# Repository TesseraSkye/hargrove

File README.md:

# Hargrove: a hybrid digital / analog synth

Built with Supercollider and Electron. 
GPL3 licence.

~~ IN DEVELOPMENT ~~

Install Supercollider and the SC3 plugins to the default directory.
https://supercollider.github.io/
https://supercollider.github.io/sc3-plugins/

 Windows firewall makes a mess of things, so add an exception:
 https://support.microsoft.com/help/4028485

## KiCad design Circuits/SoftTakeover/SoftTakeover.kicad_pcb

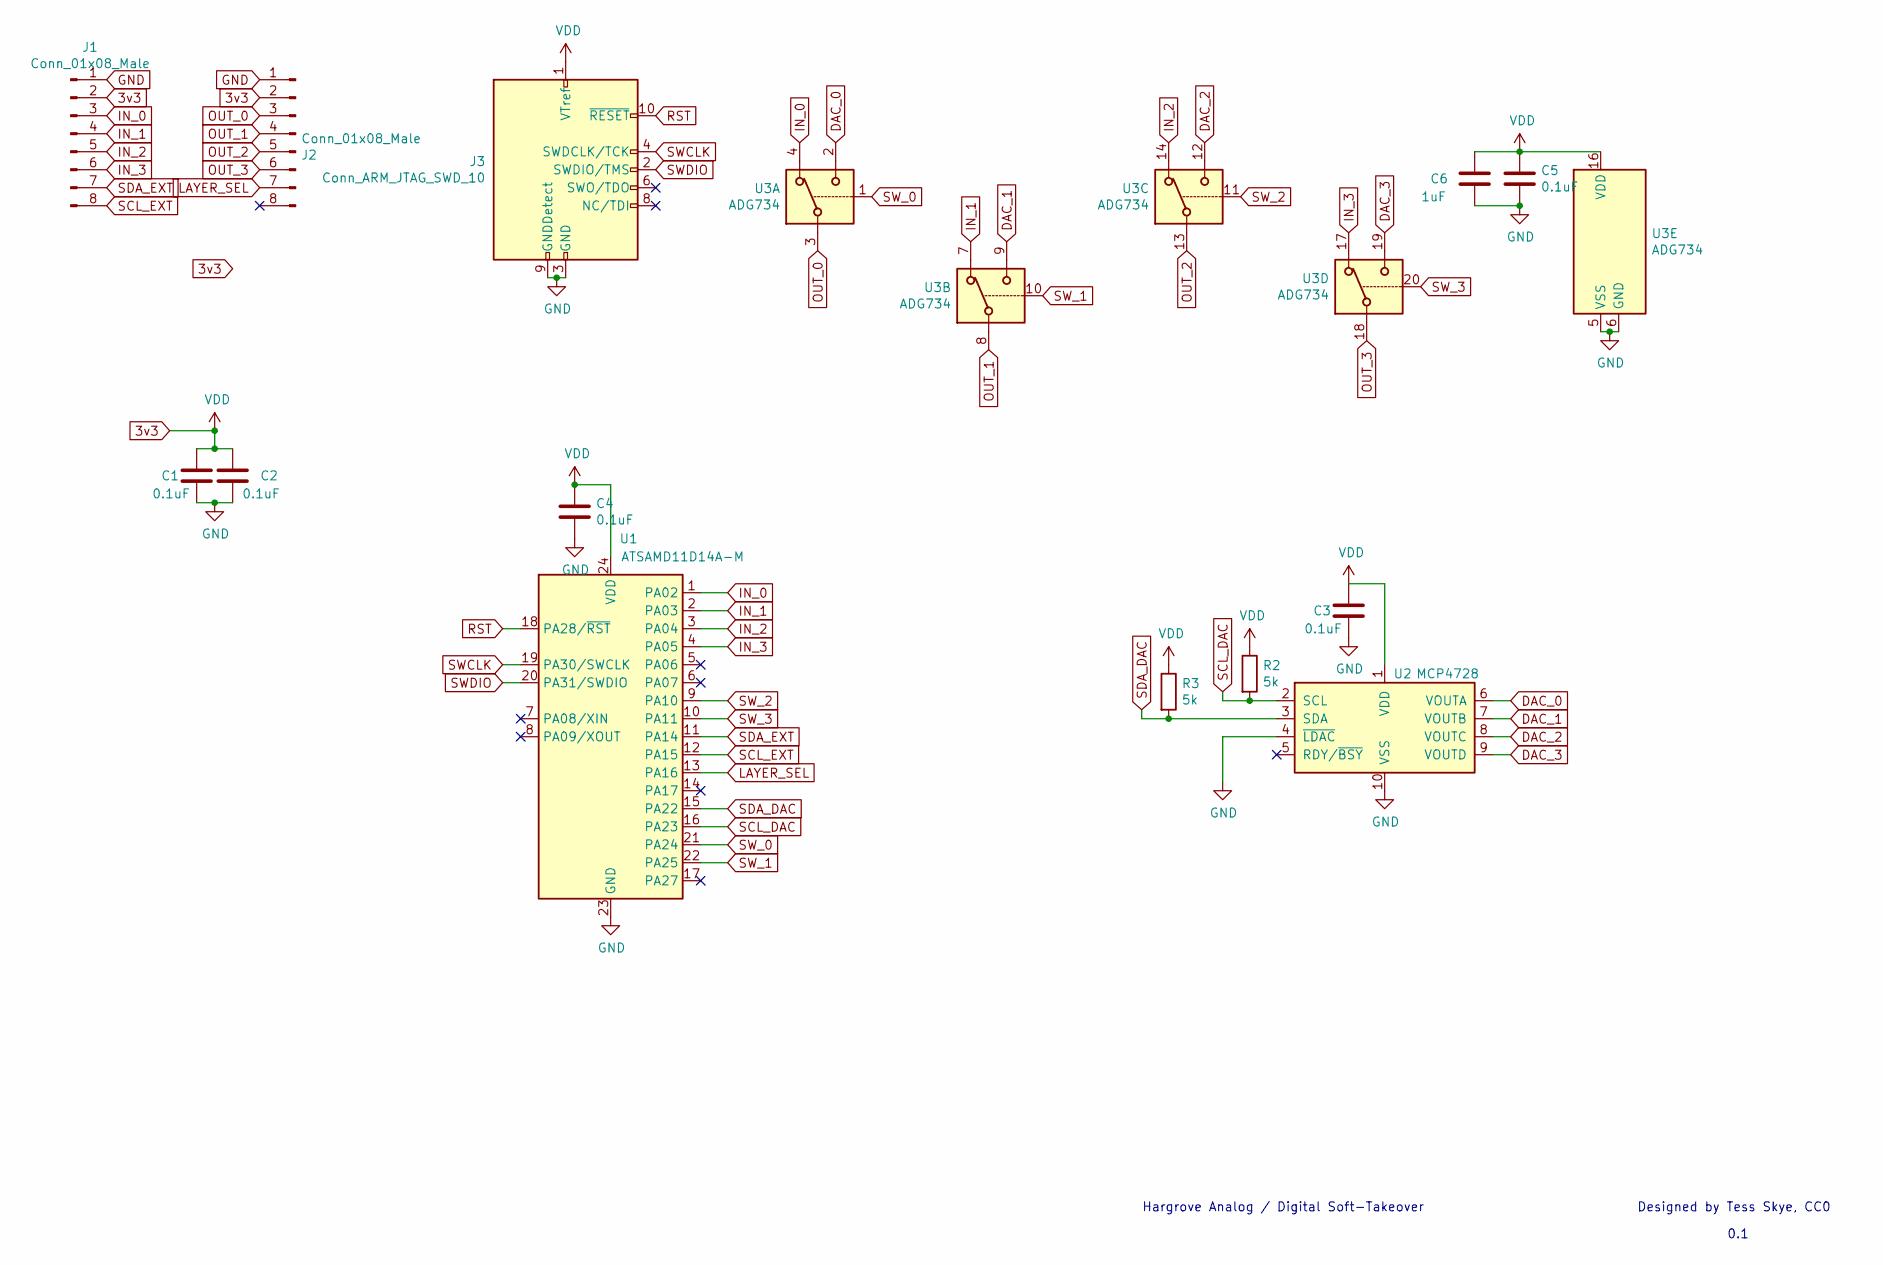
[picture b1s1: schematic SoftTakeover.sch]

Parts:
C1, C2, C3, C4, C5: 0.1uF; C_0603_1608Metric
C6: 1uF; C_0603_1608Metric
J1, J2: Conn_01x08_Male; PinHeader_1x08_P2.54mm_Vertical
J3: Conn_ARM_JTAG_SWD_10; PinHeader_2x05_P1.27mm_Vertical
R2, R3: 5k; R_0603_1608Metric
U1: ATSAMD11D14A-M; QFN-24-1EP_4x4mm_P0.5mm_EP2.6x2.6mm
U2: MCP4728; MSOP-10_3x3mm_P0.5mm
U3: ADG734; TSSOP-20_4.4x6.5mm_P0.65mm

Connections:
3v3: C1.2, C2.2, C3.2, C4.2, C5.1, C6.1, J1.2, J2.2, J3.1 (VTref), R2.1, R3.1, U1.24 (VDD), U2.1 (VDD), U3.16 (VDD)
DAC_0: U2.6 (VOUTA), U3.2
DAC_1: U2.7 (VOUTB), U3.9
DAC_2: U2.8 (VOUTC), U3.12
DAC_3: U2.9 (VOUTD), U3.19
GND: C1.1, C2.1, C3.1, C4.1, C5.2, C6.2, J1.1, J2.1, J3.3 (GND), J3.5 (GND), J3.9 (GNDDetect), U1.23 (GND), U2.4 (~LDAC), U2.10 (VSS), U3.5 (VSS), U3.6 (GND)
IN_0: J1.3, U1.1 (PA02), U3.4
IN_1: J1.4, U1.2 (PA03), U3.7
IN_2: J1.5, U1.3 (PA04), U3.14
IN_3: J1.6, U1.4 (PA05), U3.17
LAYER_SEL: J2.7, U1.13 (PA16)
OUT_0: J2.3, U3.3
OUT_1: J2.4, U3.8
OUT_2: J2.5, U3.13
OUT_3: J2.6, U3.18
RST: J3.10 (~RESET~), U1.18 (PA28/~RST)
SCL_DAC: R2.2, U1.16 (PA23), U2.2 (SCL)
SCL_EXT: J1.8, U1.12 (PA15)
SDA_DAC: R3.2, U1.15 (PA22), U2.3 (SDA)
SDA_EXT: J1.7, U1.11 (PA14)
SWCLK: J3.4 (SWDCLK/TCK), U1.19 (PA30/SWCLK)
SWDIO: J3.2 (SWDIO/TMS), U1.20 (PA31/SWDIO)
SW_0: U1.21 (PA24), U3.1
SW_1: U1.22 (PA25), U3.10
SW_2: U1.9 (PA10), U3.11
SW_3: U1.10 (PA11), U3.20

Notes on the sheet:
Hargrove Analog / Digital Soft-Takeover
Designed by Tess Skye, CC0
0.1

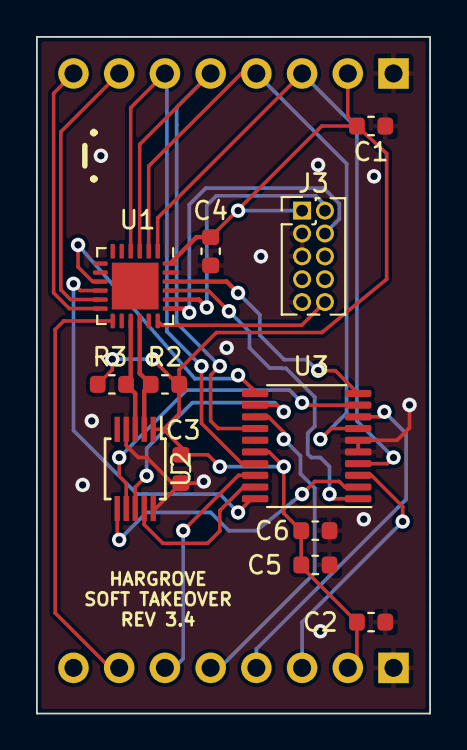
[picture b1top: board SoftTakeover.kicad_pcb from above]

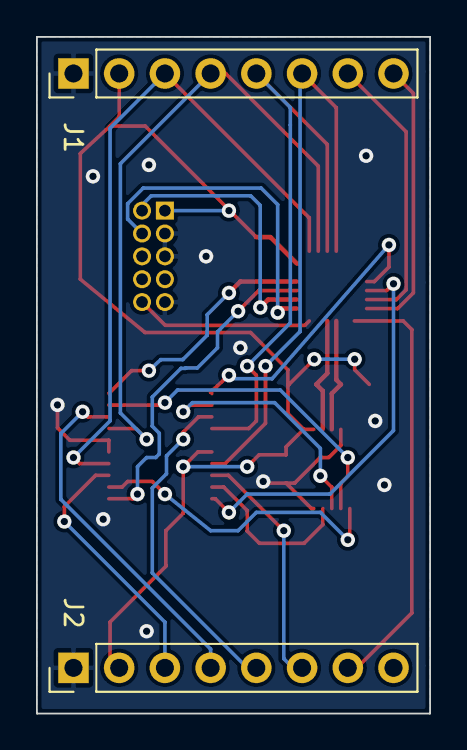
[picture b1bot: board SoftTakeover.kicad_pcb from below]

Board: 2 copper layers, 21.8 x 37.6 mm, 14 parts (2 on the bottom side), 26 nets.

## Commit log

2020-08-18 Updated with engine and samples
2020-08-18 depersonalized the sample placeholder
2020-08-19 Updated with nice electron frontend
2020-08-19 Bump electron from 2.0.18 to 7.2.4
    Bumps [electron](https://github.com/electron/electron) from 2.0.18 to 7.2.4.
    - [Release notes](https://github.com/electron/electron/releases)
    - [Changelog](https://github.com/electron/electron/blob/master/docs/breaking-changes.md)
    - [Commits](https://github.com/electron/electron/compare/v2.0.18...v7.2.4)
2020-08-20 started work on porting audio engine
2020-08-22 moved things around, restructured some backend
2020-09-02 Bump bl from 4.0.2 to 4.0.3
    Bumps [bl](https://github.com/rvagg/bl) from 4.0.2 to 4.0.3.
    - [Release notes](https://github.com/rvagg/bl/releases)
    - [Commits](https://github.com/rvagg/bl/compare/v4.0.2...v4.0.3)
2020-09-13 Bump node-fetch from 2.6.0 to 2.6.1
    Bumps [node-fetch](https://github.com/bitinn/node-fetch) from 2.6.0 to 2.6.1.
    - [Release notes](https://github.com/bitinn/node-fetch/releases)
    - [Changelog](https://github.com/node-fetch/node-fetch/blob/master/docs/CHANGELOG.md)
    - [Commits](https://github.com/bitinn/node-fetch/compare/v2.6.0...v2.6.1)
2020-10-08 Totally redid literally everything
2020-10-11 Reworked repo
2020-10-11 Added Arduino i2c util
2020-10-23 Running tests to learn scripting for rpi
2020-11-13 Did a bunch of design work
2020-12-28 Added various schematics
2020-12-29 Fixed the clicking in the sampler
